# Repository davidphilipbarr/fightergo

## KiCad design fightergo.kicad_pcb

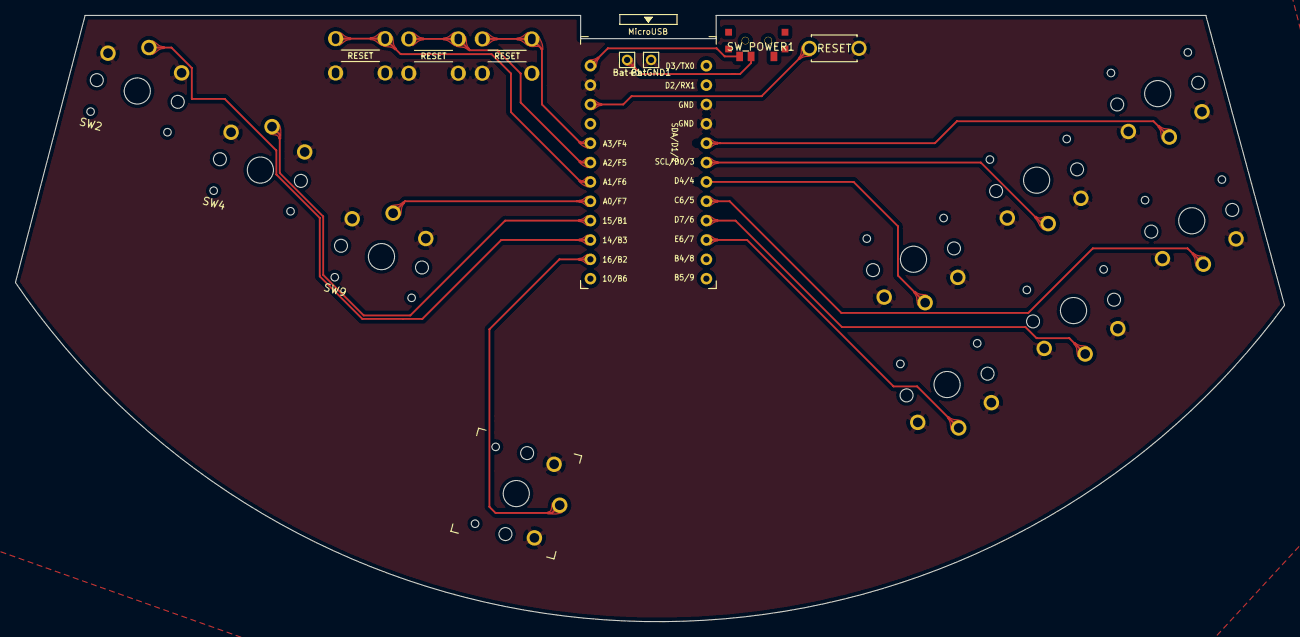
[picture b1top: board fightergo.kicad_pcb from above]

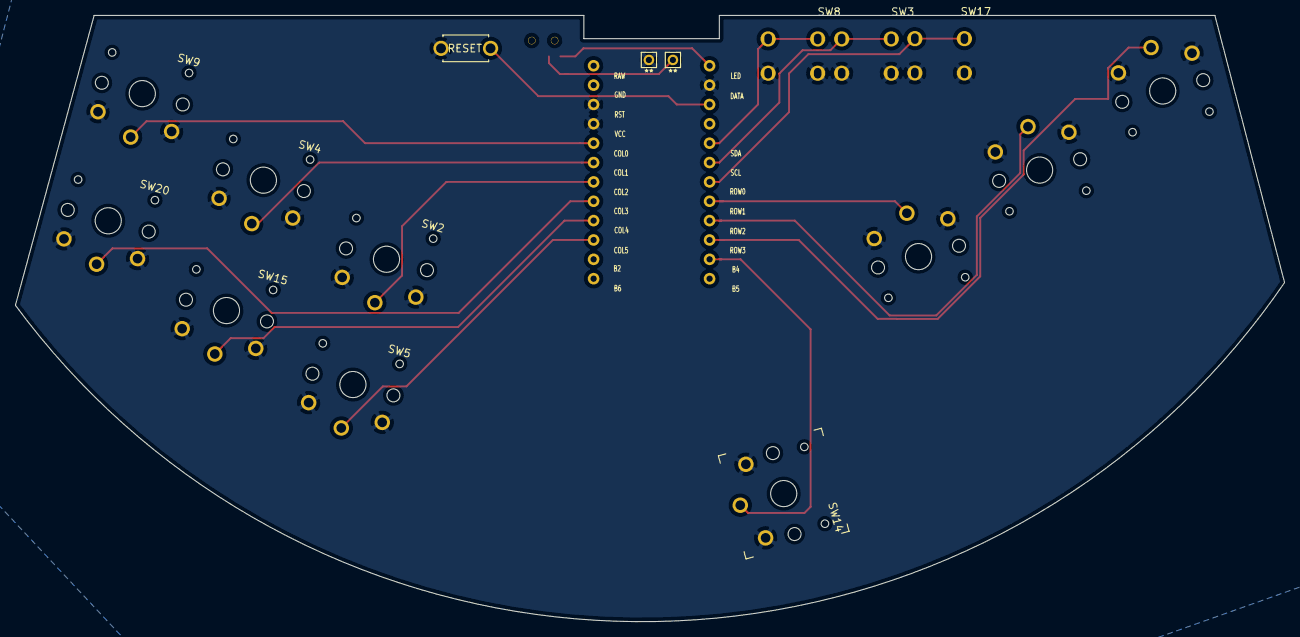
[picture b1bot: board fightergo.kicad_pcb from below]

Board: 2 copper layers, 166.5 x 79.5 mm, 18 parts (3 on the bottom side), 17 nets.

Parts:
Bat+1: MountingHole_Pad; 1pin_conn
BatGND1: MountingHole_Pad; 1pin_conn
RSW1: SW_Push; ResetSW
SW2, SW2#2, SW4, SW4#2, SW5, SW9, SW9#2, SW15, SW20: SW_Push; SW_PG1350_rev_DPB
SW3, SW8, SW17: SW_Push; ResetSW_4
SW14: SW_Push; SW_PG1350_15_reversible_b2
SW_POWER1: SW_SPDT; SPDT_C128955
U1: ProMicro-kbd; ProMicro_v3

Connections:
BT+: Bat+1.1, SW_POWER1.2
Switch1: SW15.1, U1.9
Switch2: SW9#2.1, U1.17
Switch3: SW17.1, U1.18
Switch4: SW3.1, U1.19
Switch5: SW8.1, U1.20
Switch6: SW4#2.1, U1.16
Switch7: SW2#2.1, U1.15
Switch8: SW14.1, U1.14
Switch11: SW9.1, U1.5
Switch12: SW4.1, U1.6
Switch13: SW2.1, U1.7
Switch14: SW20.1, U1.8
Switch15: SW5.1, U1.10
gnd: BatGND1.1, RSW1.1, SW2.2, SW2#2.2, SW3.2, SW4.2, SW4#2.2, SW5.2, SW8.2, SW9.2, SW9#2.2, SW14.2, SW15.2, SW17.2, SW20.2, U1.3, U1.4, U1.23
raw: SW_POWER1.3, U1.24
reset: RSW1.2, U1.22
